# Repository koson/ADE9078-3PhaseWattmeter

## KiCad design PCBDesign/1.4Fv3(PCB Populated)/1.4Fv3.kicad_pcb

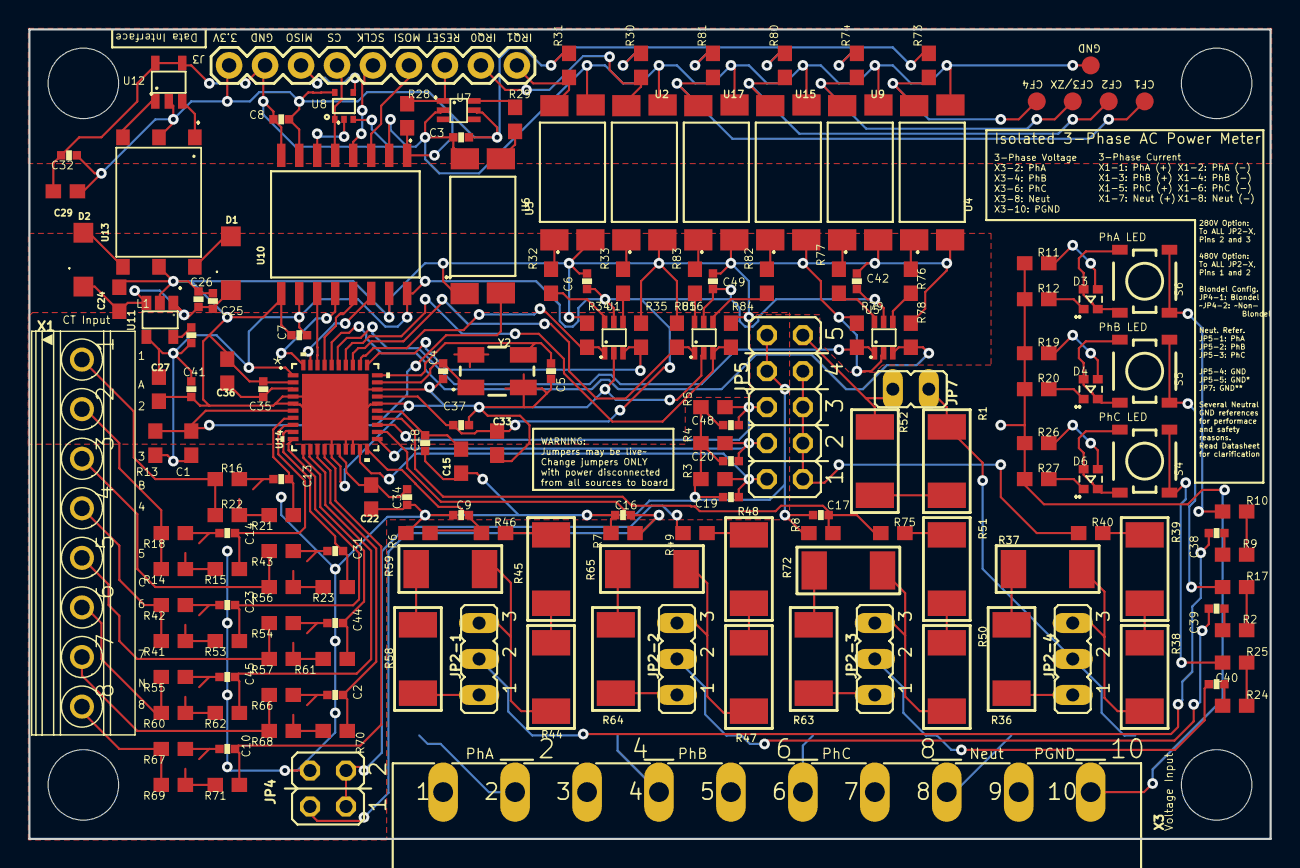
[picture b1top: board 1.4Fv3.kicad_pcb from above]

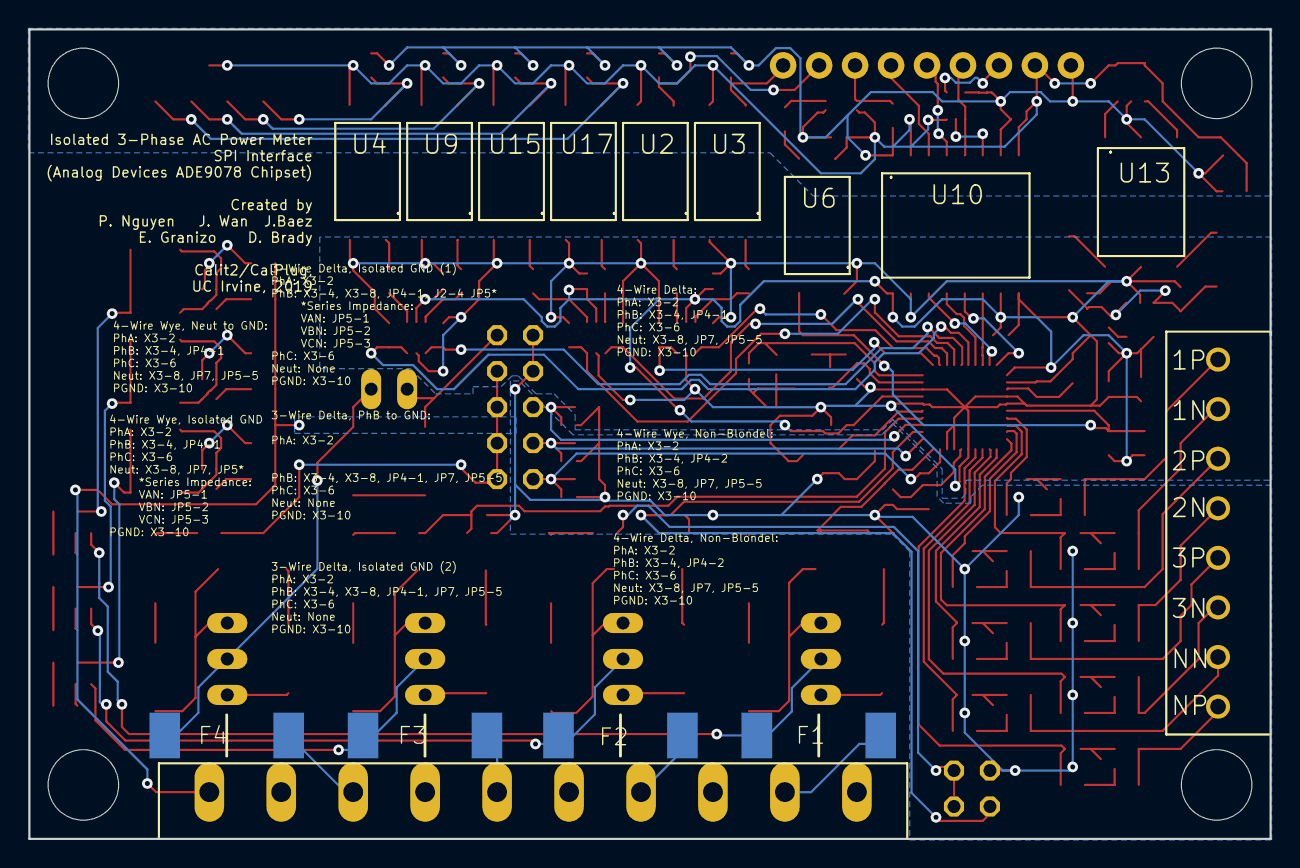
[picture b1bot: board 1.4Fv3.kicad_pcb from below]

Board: 2 copper layers, 87.6 x 57.1 mm, 176 parts (4 on the bottom side), 134 nets.

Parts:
@HOLE0, @HOLE1, @HOLE2, @HOLE3: (no value)
C1: 1uF; 0603
C2, C9, C10, C13, C14, C16, C17, C19, C20, C23, C31, C44, C45, C48: 22n; 0402-CAP
C3, C6, C7, C8, C26, C32, C37, C41, C42, C49: 0.1u; 0402-CAP
C4, C5: 30p; 0402-CAP
C15, C22, C36: 4.7uF; C0603
C18, C35: 0.22u; 0402-CAP
C24, C27, C33: 10uF; C0603
C25: 1u; 0402-CAP
C29: 10uF TANT; C0603
C34: 0.1uF; 0402-CAP
C38, C39, C40: 50n; 0402-CAP
D1, D2: MBR0520LT; SOD123
D3, D4, D6: WL-SBCW_0606
F1, F2, F3, F4: 0461.500ER; FUSC10131X312N
J3: 1X09
JP2-1, JP2-2, JP2-3, JP2-4: JP2
JP4: JP2Q
JP5: JP5Q
JP7: JP1
L1: 15nH; 0402-RES
R1, R52: 300k; R2010
R2, R9, R10, R17, R24, R25: 5k; 0603
R3, R4, R5, R6, R7, R8, R15, R21, R23, R53, R61, R62, R70, R71: 1k; 0603
R11, R12, R19, R20, R26, R27: 2k; 0603
R13, R28, R30, R31, R73, R74, R80, R81: 4.7k; 0603
R14, R22, R41, R56, R57, R60, R68, R69: 0; 0603
R16, R18, R42, R43, R54, R55, R66, R67: 20; 0603
R29, R32, R33, R76, R77, R82, R83: 560; 0603
R34, R35, R78, R79, R84, R85: 10k; 0603
R36, R37, R58, R59, R63, R64, R65, R72: 245k; R2010
R38, R39, R44, R45, R47, R48, R50, R51: 120k; R2010
R40, R46, R49, R75: 120k; 0603
S4, S5, S6: MOMENTARY-SWITCH-SPST-SMD-4.5MM; TACTILE_SWITCH_SMD_4.5MM
TP1, TP2, TP3, TP4, TP5: PTR1B1,27; B1,27
U1, U5, U7, U16: SN74LVC; DCKT
U2, U3, U4, U6, U9, U15, U17: PS2505
U8: NL17SZ125
U10: ISO7241; 16-SOIC
U11: PAM2305; TSOT25
U12: SN6501; SOT-23-5
U13: TRANSFO_3.3
U14: ADE9078; CP_40_7
X1: 1751303
X3: MSTBA10
Y2: 12.288MHz; CRYSTAL-SMD-5X3.2-4PAD

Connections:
AGND: C2.1, C9.2, C10.2, C13.1, C14.2, C15.2, C16.2, C17.2, C18.1, C19.2, C20.2, C22.2, C23.2, C31.1, C34.1, C44.1, C45.2, C48.2, JP4.4, JP5.8, JP5.10, R3.1, R4.1, R5.1, R6.1, R7.1, R8.1, R16.1, R18.2, R42.2, R43.1, R54.1, R55.1, R66.1, R67.2
AVDDOUT: C15.1, C18.2, U14.25
CF1_ISO: R85.2, U14.33, U16.1
CF1_OUT: R81.2, TP4.TP, U17.4
CF2_ISO: R84.1, U14.34, U16.3
CF2_OUT: R80.1, TP3.TP, U15.4
CF3/ZX_ISO: R79.2, U5.1, U14.35
CF3/ZX_OUT: R74.1, TP2.TP, U9.4
CF4_ISO: R78.1, U5.3, U14.36
CF4_OUT: R73.1, TP1.TP, U4.4
CS: J3.4, U8.1, U10.5
CS_ISO: U10.12, U14.40
DVDDOUT: C35.2, C36.1, U14.3
GND: C3.2, C8.2, C29.2, C32.1, J3.2, TP5.TP, U2.3, U3.3, U4.3, U6.2, U7.2, U8.3, U9.3, U10.2, U10.8, U12.4, U12.5, U15.3, U17.3
GNDI: C4.1, C5.2, C6.1, C7.1, C24.2, C25.1, C26.1, C27.2, C33.2, C35.1, C36.2, C37.1, C41.2, C42.1, C49.1, R34.1, R35.2, R78.2, R79.1, R84.2, R85.1, U1.2, U2.2, U3.2, U4.2, U5.2, U6.3, U9.2, U10.9, U10.15, U11.2, U13.5, U14.2, U14.4, U14.5, U14.15, U14.17, U14.18, U14.26, U14.28, U14.41, U15.2, U16.2, U17.2
I1N: R14.1, R18.1, X1.2
I1P: R16.2, R22.1, X1.1
I2N: R41.1, R42.1, X1.4
I2P: R43.2, R56.1, X1.3
I3N: R55.2, R60.1, X1.6
I3P: R54.2, R57.1, X1.5
IAN: C14.1, R15.2, U14.8
IAP\: C13.2, R21.2, U14.7
IBN: C23.1, R53.2, U14.10
IBP: C31.2, R23.2, U14.9
ICN: C45.1, R62.2, U14.12
ICP: C44.2, R61.2, U14.11
INN: C10.1, R71.2, U14.14
INP: C2.2, R70.2, U14.13
IRQ0_ISO: R35.1, U1.3, U14.31
IRQ0_OUT: J3.8, R30.1, U2.4
IRQ1_ISO: R34.2, U1.1, U14.32
IRQ1_OUT: J3.9, R31.1, U3.4
I_NEUT_N: R67.1, R69.1, X1.8
I_NEUT_P: R66.2, R68.1, X1.7
MISO: U8.2, U10.6
MISO_ISO: U10.11, U14.38
MISO_OUT: J3.3, U8.4
MOSI: J3.6, U10.3
MOSI_ISO: U10.14, U14.39
unnamed: C5.1, U14.30, Y2.3
unnamed: R21.1, R22.2
unnamed: R14.2, R15.1
unnamed: L1.1, U11.5
unnamed: R57.2, R61.1
unnamed: R60.2, R62.1
unnamed: C38.2, R9.1
unnamed: R32.2, U1.6
unnamed: R32.1, U3.1
unnamed: C4.2, U14.29, Y2.1
unnamed: R25.2, S4.1, S4.4
unnamed: D1.A, U13.6
unnamed: C24.1, C25.2, C26.2, D1.C, D2.C, U11.1, U11.3
unnamed: D2.A, U13.4
unnamed: U12.3, U13.1
unnamed: U12.1, U13.3
unnamed: R23.1, R56.2
unnamed: R29.2, U6.1
unnamed: R29.1, U7.6
unnamed: R41.2, R53.1
unnamed: R9.2, R10.1
unnamed: R33.2, U1.4
unnamed: R76.2, U5.4
unnamed: R1.2, R52.1
unnamed: R64.2, R65.1
unnamed: R33.1, U2.1
unnamed: JP2-1.1, R58.1
unnamed: R58.2, R59.1
unnamed: R10.2, S6.1, S6.4
unnamed: JP2-1.3, R44.1, R59.2
unnamed: JP2-2.1, R64.1
unnamed: JP2-2.3, R47.1, R65.2
unnamed: R63.2, R72.1
unnamed: R68.2, R70.1
unnamed: JP2-4.3, R37.2, R38.1
unnamed: JP2-4.1, R36.1
unnamed: R36.2, R37.1
unnamed: JP5.9, JP7.2, R52.2
unnamed: R69.2, R71.1
unnamed: C39.2, R2.1
unnamed: R2.2, R17.1
unnamed: R17.2, S5.1, S5.4
unnamed: D3.1, R12.1
unnamed: D6.2, D6.3, S4.2, S4.3
unnamed: C40.2, R24.1
unnamed: R24.2, R25.1
unnamed: D3.4, R11.2
unnamed: D4.2, D4.3, S5.2, S5.3
unnamed: R76.1, U4.1
unnamed: R77.1, U9.1
unnamed: R77.2, U5.6
unnamed: JP5.1, JP5.3, JP5.5, JP5.7, R40.2
unnamed: R82.1, U15.1
unnamed: R83.1, U17.1
unnamed: R83.2, U16.6
unnamed: D3.2, D3.3, S6.2, S6.3
unnamed: D4.4, R19.2
unnamed: R45.2, R46.1
unnamed: C40.1, F3.1, JP2-3.2
unnamed: F4.1, JP2-4.2, JP7.1, R1.1
unnamed: C38.1, F1.1, JP2-1.2
unnamed: R48.2, R49.1
unnamed: JP2-3.3, R50.1, R72.2
unnamed: JP4.1, JP4.3, R49.2
unnamed: C39.1, F2.1, JP2-2.2
unnamed: JP2-3.1, R63.1
unnamed: R50.2, R51.1
unnamed: R51.2, R75.1
unnamed: R82.2, U16.4
unnamed: R44.2, R45.1
unnamed: R47.2, R48.1
unnamed: R38.2, R39.1
unnamed: R39.2, R40.1
unnamed: D4.1, R20.1
unnamed: D6.1, R27.2
unnamed: D6.4, R26.2
NEUT: F4.2, X3.8
PGROUND: R11.1, R12.2, R19.1, R20.2, R26.1, R27.1, X3.10
REF: C22.1, C34.2, U14.16
RESET: J3.7, R28.2, U7.1
RESET_ISO: C1.2, R13.1, U6.4, U14.6
SCLK: J3.5, U10.4
SCLK_ISO: U10.13, U14.37
VAN: C19.1, JP5.2, R3.2, U14.19
VAP: C9.1, R6.2, R46.2, U14.20
VBN: C20.1, JP5.4, R4.2, U14.21
VBP: C16.1, JP4.2, R7.2, U14.22
VCC: C1.1, C6.2, C7.2, C27.1, C33.1, C37.2, C41.1, C42.2, C49.2, L1.2, R13.2, U1.5, U5.5, U10.10, U10.16, U11.4, U14.1, U14.27, U16.5
VCN: C48.1, JP5.6, R5.2, U14.23
VCP: C17.1, R8.2, R75.2, U14.24
VDD: C3.1, C8.1, C29.1, C32.2, J3.1, R28.1, R30.2, R31.2, R73.2, R74.2, R80.2, R81.1, U7.5, U8.5, U10.1, U10.7, U12.2, U13.2
V_PH_A: F1.2, X3.2
V_PH_B: F2.2, X3.4
V_PH_C: F3.2, X3.6

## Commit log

2023-02-11 convert tp Kicad
